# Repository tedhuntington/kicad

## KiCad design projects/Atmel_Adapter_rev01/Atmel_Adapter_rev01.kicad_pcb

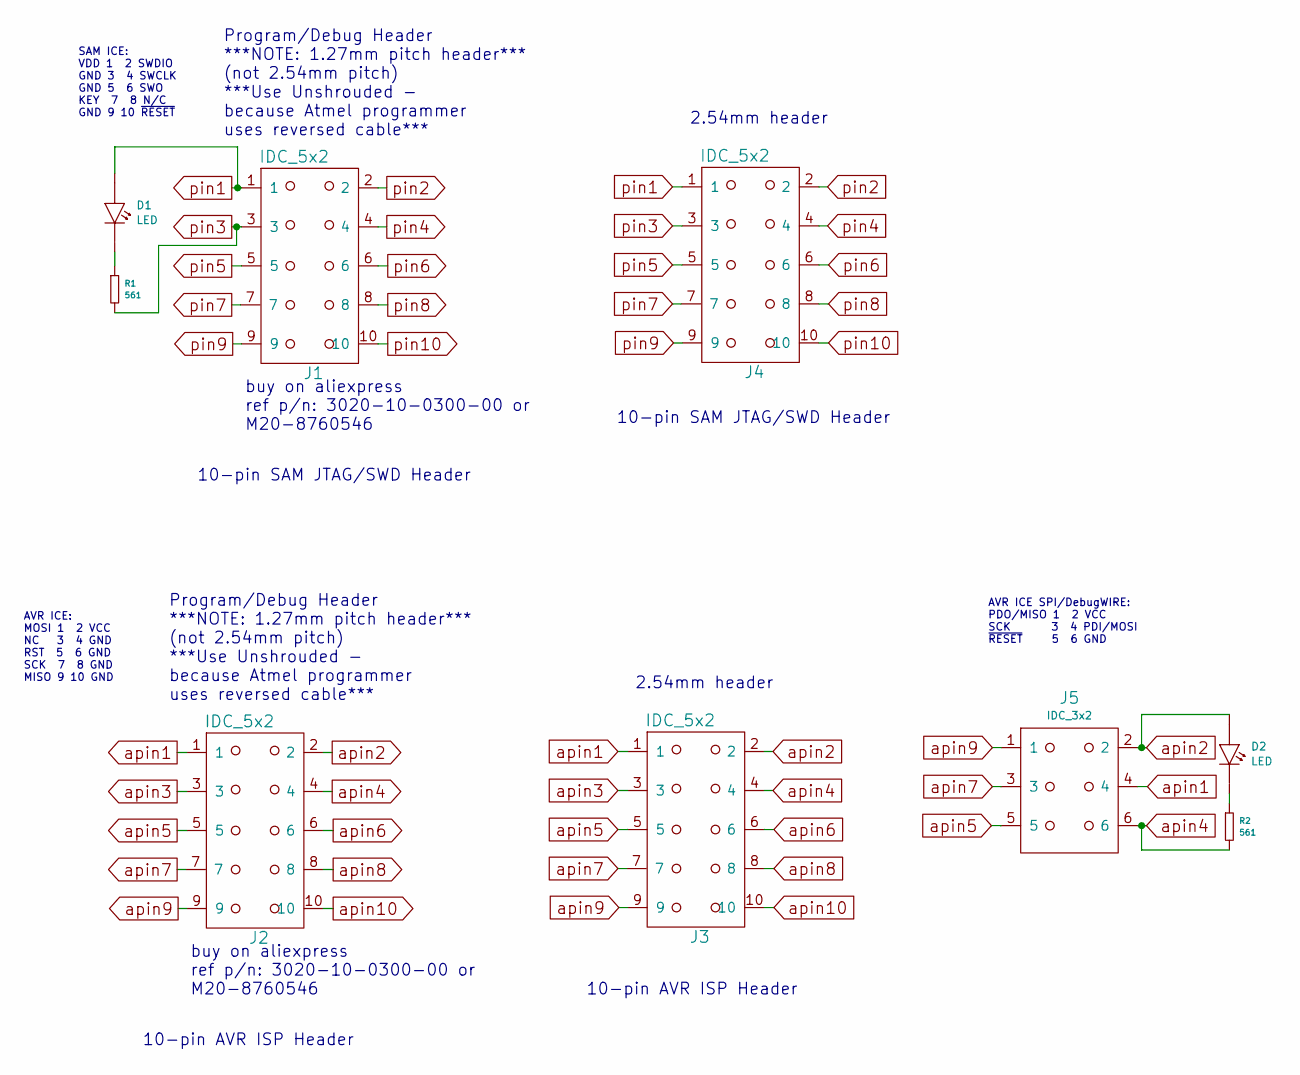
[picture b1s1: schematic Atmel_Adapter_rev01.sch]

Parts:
D1, D2: LED; TED_SM1206_LED
J1, J2: IDC_5x2; TED_IDC_5x2_1.27pitch_SMD_nm
J3, J4: IDC_5x2; TED_IDC_5x2_SMD
J5: IDC_3x2; TED_IDC_3x2_SMD
R1, R2: 561; TED_SM0603_R

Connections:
unnamed: D1.2 (K), R1.1
unnamed: D2.2 (K), R2.1
apin1: J2.1, J3.1, J5.4
apin2: D2.1 (A), J2.2, J3.2, J5.2
apin3: J2.3, J3.3
apin4: J2.4, J3.4, J5.6, R2.2
apin5: J2.5, J3.5, J5.5
apin6: J2.6, J3.6
apin7: J2.7, J3.7, J5.3
apin8: J2.8, J3.8
apin9: J2.9, J3.9, J5.1
apin10: J2.10, J3.10
pin1: D1.1 (A), J1.1, J4.1
pin2: J1.2, J4.2
pin3: J1.3, J4.3, R1.2
pin4: J1.4, J4.4
pin5: J1.5, J4.5
pin6: J1.6, J4.6
pin7: J1.7, J4.7
pin8: J1.8, J4.8
pin9: J1.9, J4.9
pin10: J1.10, J4.10

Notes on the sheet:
Program/Debug Header ***NOTE: 1.27mm pitch header*** (not 2.54mm pitch) ***Use Unshrouded - because Atmel programmer uses reversed cable***
buy on aliexpress ref p/n: 3020-10-0300-00 or M20-8760546
SAM ICE: VDD 1 2 SWDIO GND 3 4 SWCLK GND 5 6 SWO KEY 7 8 N/C GND 9 10 ~RESET
10-pin SAM JTAG/SWD Header
2.54mm header
AVR ICE: MOSI 1 2 VCC NC 3 4 GND RST 5 6 GND SCK 7 8 GND MISO 9 10 GND
10-pin AVR ISP Header
AVR ICE SPI/DebugWIRE: PDO/MISO 1 2 VCC SCK 3 4 PDI/MOSI ~RESET~ 5 6 GND

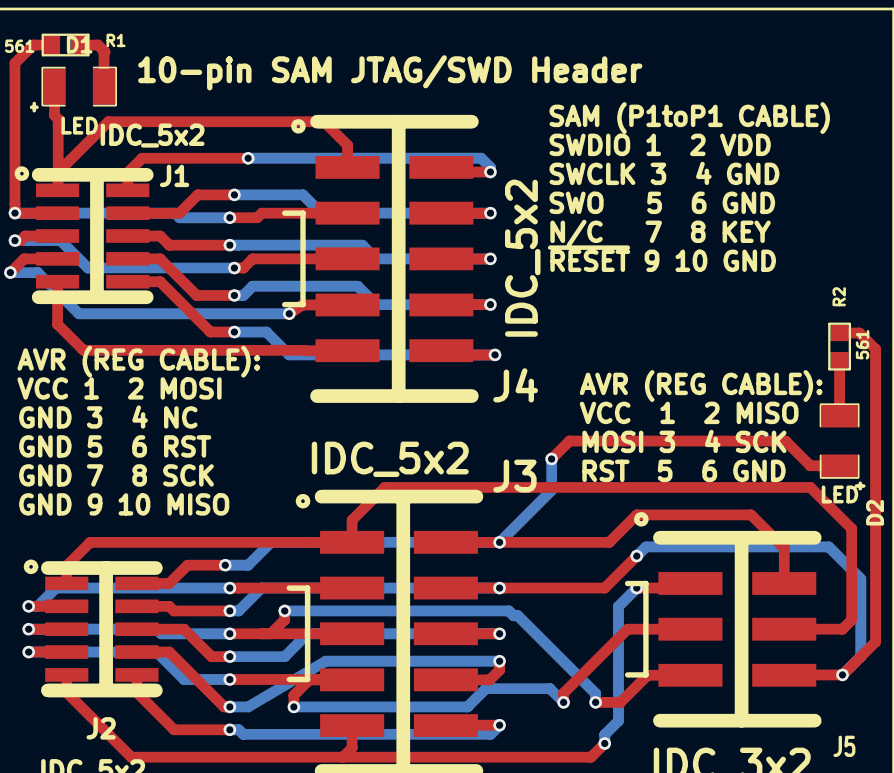
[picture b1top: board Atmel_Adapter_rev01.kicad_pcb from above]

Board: 2 copper layers, 9 parts (0 on the bottom side), 22 nets.
